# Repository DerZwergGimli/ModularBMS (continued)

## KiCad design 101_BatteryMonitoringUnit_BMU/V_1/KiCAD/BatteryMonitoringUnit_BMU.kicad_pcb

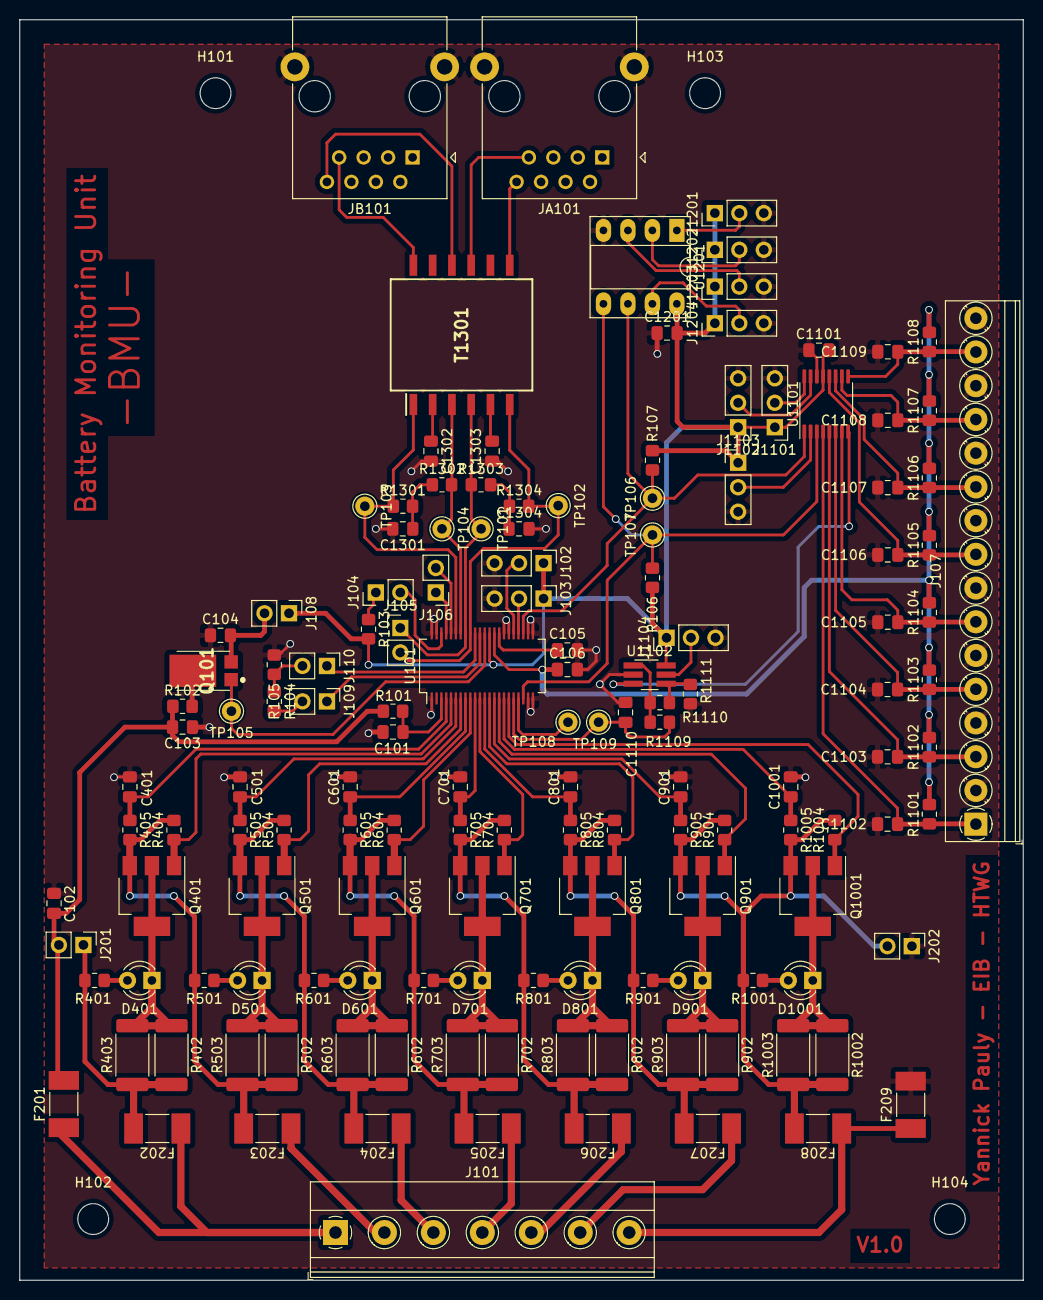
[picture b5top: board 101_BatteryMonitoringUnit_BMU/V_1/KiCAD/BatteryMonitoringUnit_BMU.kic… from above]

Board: 2 copper layers, 104.1 x 130.8 mm, 149 parts (0 on the bottom side), 96 nets.

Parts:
C101, C1101, C1201: 100nF; C_0805_2012Metric_Pad1.18x1.45mm_HandSolder
C102, C1102, C1103, C1104, C1105, C1106, C1107, C1108, C1109: 10nF*; C_0805_2012Metric_Pad1.18x1.45mm_HandSolder
C103: 0.1u; C_0805_2012Metric_Pad1.18x1.45mm_HandSolder
C104, C105, C106: 1uF; C_0805_2012Metric_Pad1.18x1.45mm_HandSolder
C401, C501, C601, C701, C801, C901, C1001: 10nF/30V; C_0805_2012Metric_Pad1.18x1.45mm_HandSolder
C1110, C1301, C1302, C1303, C1304: 10nF; C_0805_2012Metric_Pad1.18x1.45mm_HandSolder
D401, D501, D601, D701, D801, D901, D1001: LED_Dis; LED_D3.0mm
F201, F209: Fuse_0.5A; Fuse_Littelfuse-NANO2-451_453
F202, F203, F204, F205, F206, F207, F208: Fuse_0.25A; Fuse_Littelfuse-NANO2-451_453
H101, H102, H103, H104: MountingHole; MountingHole_3.2mm_M3_DIN965
J101: BalancingConnect; TerminalBlock_Phoenix_MKDS-1,5-7-5.08_1x07_P5.08mm_Horizont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
J102: isoSPI/SPI; PinHeader_1x03_P2.54mm_Vertical
J103: DischargeTimer; PinHeader_1x03_P2.54mm_Vertical
J104: WatchdogTimer; PinHeader_1x02_P2.54mm_Vertical
J105: SerialInterface_1; PinHeader_1x02_P2.54mm_Vertical
J106: SerialInterface_0; PinHeader_1x02_P2.54mm_Vertical
J107: NTC_10k; TerminalBlock_Phoenix_PT-1,5-16-3.5-H_1x16_P3.50mm_Horizont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
J108: V_REG; PinHeader_1x02_P2.54mm_Vertical
J109: I_BIAS; PinHeader_1x02_P2.54mm_Vertical
J110: I_CMP; PinHeader_1x02_P2.54mm_Vertical
J201: FusedBATT+; PinHeader_1x02_P2.54mm_Vertical
J202: FusedBATT-; PinHeader_1x02_P2.54mm_Vertical
J1101: Temp_A0; PinHeader_1x03_P2.54mm_Vertical
J1102: Temp_A1; PinHeader_1x03_P2.54mm_Vertical
J1103: Temp_~RESET; PinHeader_1x03_P2.54mm_Vertical
J1104: Temp_~SHDN; PinHeader_1x03_P2.54mm_Vertical
J1201: EEPROM_A0; PinHeader_1x03_P2.54mm_Vertical
J1202: EEPROM_A1; PinHeader_1x03_P2.54mm_Vertical
J1203: EEPROM_A2; PinHeader_1x03_P2.54mm_Vertical
J1204: EEPROM_~ENABLE; PinHeader_1x03_P2.54mm_Vertical
JA101: isoSPI_IN; RJ45_C
JB101: isoSPI_OUT; RJ45_C
Q101: DXT5551P5-13; DXT5551P513
Q401, Q501, Q601, Q701, Q801, Q901, Q1001: PZT2222A; SOT-223-3_TabPin2
R101: 10; R_0805_2012Metric_Pad1.20x1.40mm_HandSolder
R102, R405, R505, R605, R705, R805, R905, R1005, R1109: 100; R_0805_2012Metric_Pad1.20x1.40mm_HandSolder
R103: 1M; R_0805_2012Metric_Pad1.20x1.40mm_HandSolder
R104, R105, R404, R504, R604, R704, R804, R904, R1004: 1k; R_0805_2012Metric_Pad1.20x1.40mm_HandSolder
R106, R107, R1101, R1102, R1103, R1104, R1105, R1106, R1107, R1108, R1111: 10k; R_0805_2012Metric_Pad1.20x1.40mm_HandSolder
R401, R501, R601, R701, R801, R901, R1001: Rv_LED; R_0805_2012Metric_Pad1.20x1.40mm_HandSolder
R402, R403, R502, R503, R602, R603, R702, R703, R802, R803, R902, R903, R1002, R1003: R_Dis; R_2512_6332Metric_Pad1.40x3.35mm_HandSolder
R1110: 0; R_0805_2012Metric_Pad1.20x1.40mm_HandSolder
R1301, R1302, R1303, R1304: 49.9; R_0805_2012Metric_Pad1.20x1.40mm_HandSolder
T1301: HM2112ZNL; SOP200P1543X320-12N
TP101, TP102, TP103, TP104, TP105, TP106, TP107, TP108, TP109: TestPoint; Pin_D1.0mm_L10.0mm
U101: LTC6810-1_mod; SSOP-44_5.3x12.8mm_P0.5mm
U1101: ADG728; TSSOP-16_4.4x5mm_P0.65mm
U1102: LTC6255; TSOT-23-6_HandSoldering
U1201: 24LC256; DIP-8_W7.62mm_Socket_LongPads

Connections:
+BATT: F201.1, F202.1, J101.1
-BATT: F208.1, F209.1, J101.7
/BalanceFuses/FusedCell_0: F208.2, J202.2, Q901.3, Q1001.3, R904.2, R905.2, R1001.1, R1002.2, R1003.1, R1004.2, R1005.2
/BalanceFuses/FusedCell_1: F207.2, Q801.3, R804.2, R805.2, R901.1, R902.2, R903.1
/BalanceFuses/FusedCell_2: F206.2, Q701.3, R704.2, R705.2, R801.1, R802.2, R803.1
/BalanceFuses/FusedCell_3: F205.2, Q601.3, R604.2, R605.2, R701.1, R702.2, R703.1
/BalanceFuses/FusedCell_4: F204.2, Q501.3, R504.2, R505.2, R601.1, R602.2, R603.1
/BalanceFuses/FusedCell_5: F203.2, Q401.3, R404.2, R405.2, R501.1, R502.2, R503.1
/BalanceFuses/FusedCell_6: F202.2, J201.1, R401.1, R402.2, R403.1
/C_0: C1001.1, R1005.1, U101.16
/C_1: C901.1, R905.1, U101.14
/C_2: C801.1, R805.1, U101.12
/C_3: C701.1, R705.1, U101.10
/C_4: C601.1, R605.1, U101.8
/C_5: C501.1, R505.1, U101.6
/C_6: C401.1, R405.1, U101.4
/Cell_1: F207.1, J101.6
/Cell_2: F206.1, J101.5
/Cell_3: F205.1, J101.4
/Cell_4: F204.1, J101.3
/Cell_5: F203.1, J101.2
/EEPROM_I2C/A0: J1201.2, U1201.1
/EEPROM_I2C/A1: J1202.2, U1201.2
/EEPROM_I2C/A2: J1203.2, U1201.3
/EEPROM_I2C/~ENABLE: J1204.2, U1201.7
/MUX_I2C/A0: J1101.2, U1101.16
/MUX_I2C/A1: J1102.2, U1101.15
/MUX_I2C/~RESET: J1103.2, U1101.2
/MUX_I2C/~SHDN: J1104.2, U1102.5
/NTC_0: C1102.1, J107.1, R1101.1, U1101.4
/NTC_1: C1103.1, J107.3, R1102.1, U1101.5
/NTC_2: C1104.1, J107.5, R1103.1, U1101.6
/NTC_3: C1105.1, J107.7, R1104.1, U1101.7
/NTC_4: C1106.1, J107.9, R1105.1, U1101.12
/NTC_5: C1107.1, J107.11, R1106.1, U1101.11
/NTC_6: C1108.1, J107.13, R1107.1, U1101.10
/NTC_7: C1109.1, J107.15, R1108.1, U1101.9
/S_0: Q1001.1, R1004.1, U101.17
/S_1: Q901.1, R904.1, U101.15
/S_2: Q801.1, R804.1, U101.13
/S_3: Q701.1, R704.1, U101.11
/S_4: Q601.1, R604.1, U101.9
/S_5: Q501.1, R504.1, U101.7
/S_6: Q401.1, R404.1, U101.5
/isoSPI/isoSPI_IN+_Header: JA101.7, T1301.9
/isoSPI/isoSPI_IN-_Header: JA101.8, T1301.7
/isoSPI/isoSPI_OUT+_Header: JB101.7, T1301.12
/isoSPI/isoSPI_OUT-_Header: JB101.8, T1301.10
DRIVE: Q101.1, TP105.1, U101.33
DTEN: J103.2, U101.26
GND: C101.1, C102.2, C103.1, C104.1, C105.2, C106.2, C401.2, C501.2, C601.2, C701.2, C801.2, C901.2, C1001.2, C1101.1, C1102.2, C1103.2, C1104.2, C1105.2, C1106.2, C1107.2, C1108.2, C1109.2, C1110.2, C1201.1, C1301.2, C1302.2, C1303.1, C1304.2, F209.2, J102.3, J103.3, J107.2, J107.4, J107.6, J107.8, J107.10, J107.12, J107.14, J107.16, J202.1, J1101.3, J1102.3, J1103.3, J1104.3, J1201.3, J1202.3, J1203.3, J1204.3, JA101.SH, JB101.SH, R105.1, R1111.2, U101.1, U101.21, U101.22, U101.23, U101.24, U101.28, U101.29, U101.43, U101.44, U1101.14, U1102.2, U1201.4
GPIO1_(ADC): C1110.1, R1109.2, TP109.1, U101.18
GPIO2_(ADC): TP108.1, U101.19
GPIO3_(SDA): R106.1, TP107.1, U101.20, U1101.3, U1201.5
GPIO4_(SCL): R107.1, TP106.1, U101.25, U1101.1, U1201.6
IBIAS: J109.1, U101.34
ICMP: J110.1, U101.35
ISOMD: J102.2, U101.27
unnamed: C101.2, R101.1, U101.3
unnamed: C104.2, J108.2, Q101.2
unnamed: C1301.1, R1301.2, R1302.1
unnamed: C1302.1, T1301.2
unnamed: C1303.2, T1301.5
unnamed: C1304.1, R1303.2, R1304.1
unnamed: D401.1, Q401.2, R402.1, R403.2
unnamed: D401.2, R401.2
unnamed: D501.1, Q501.2, R502.1, R503.2
unnamed: D501.2, R501.2
unnamed: D601.1, Q601.2, R602.1, R603.2
unnamed: D601.2, R601.2
unnamed: D701.1, Q701.2, R702.1, R703.2
unnamed: D701.2, R701.2
unnamed: D801.1, Q801.2, R802.1, R803.2
unnamed: D801.2, R801.2
unnamed: D901.1, Q901.2, R902.1, R903.2
unnamed: D901.2, R901.2
unnamed: D1001.1, Q1001.2, R1002.1, R1003.2
unnamed: D1001.2, R1001.2
unnamed: J104.1, R103.1
unnamed: J109.2, R104.2
unnamed: J110.2, R104.1, R105.2
unnamed: Q101.3, R102.2
unnamed: R1109.1, R1110.1, U1102.1
unnamed: R1110.2, R1111.1, U1102.4
unnamed: U1101.8, U1102.3
Serial_CLK: J106.1, U101.41
Serial_MISO: J105.1, R1303.1, T1301.4, TP101.1, U101.37
Serial_MOSI: J106.2, U101.40
Serial_~CS: J105.2, R1304.2, T1301.6, TP102.1, U101.36
VCC: C102.1, C103.2, F201.2, J201.2, R101.2, R102.1
V_Ref1: C105.1, U101.30
V_Ref2: C106.1, R1101.2, R1102.2, R1103.2, R1104.2, R1105.2, R1106.2, R1107.2, R1108.2, U101.31
V_Reg: C1101.2, C1201.2, J102.1, J103.1, J108.1, J1101.1, J1102.1, J1103.1, J1104.1, J1201.1, J1202.1, J1203.1, J1204.1, R103.2, R106.2, R107.2, U101.32, U1101.13, U1102.6, U1201.8
WDT: J104.2, U101.42
isoSPI+_OUT: R1301.1, T1301.1, TP103.1, U101.39
isoSPI-_OUT: R1302.2, T1301.3, TP104.1, U101.38

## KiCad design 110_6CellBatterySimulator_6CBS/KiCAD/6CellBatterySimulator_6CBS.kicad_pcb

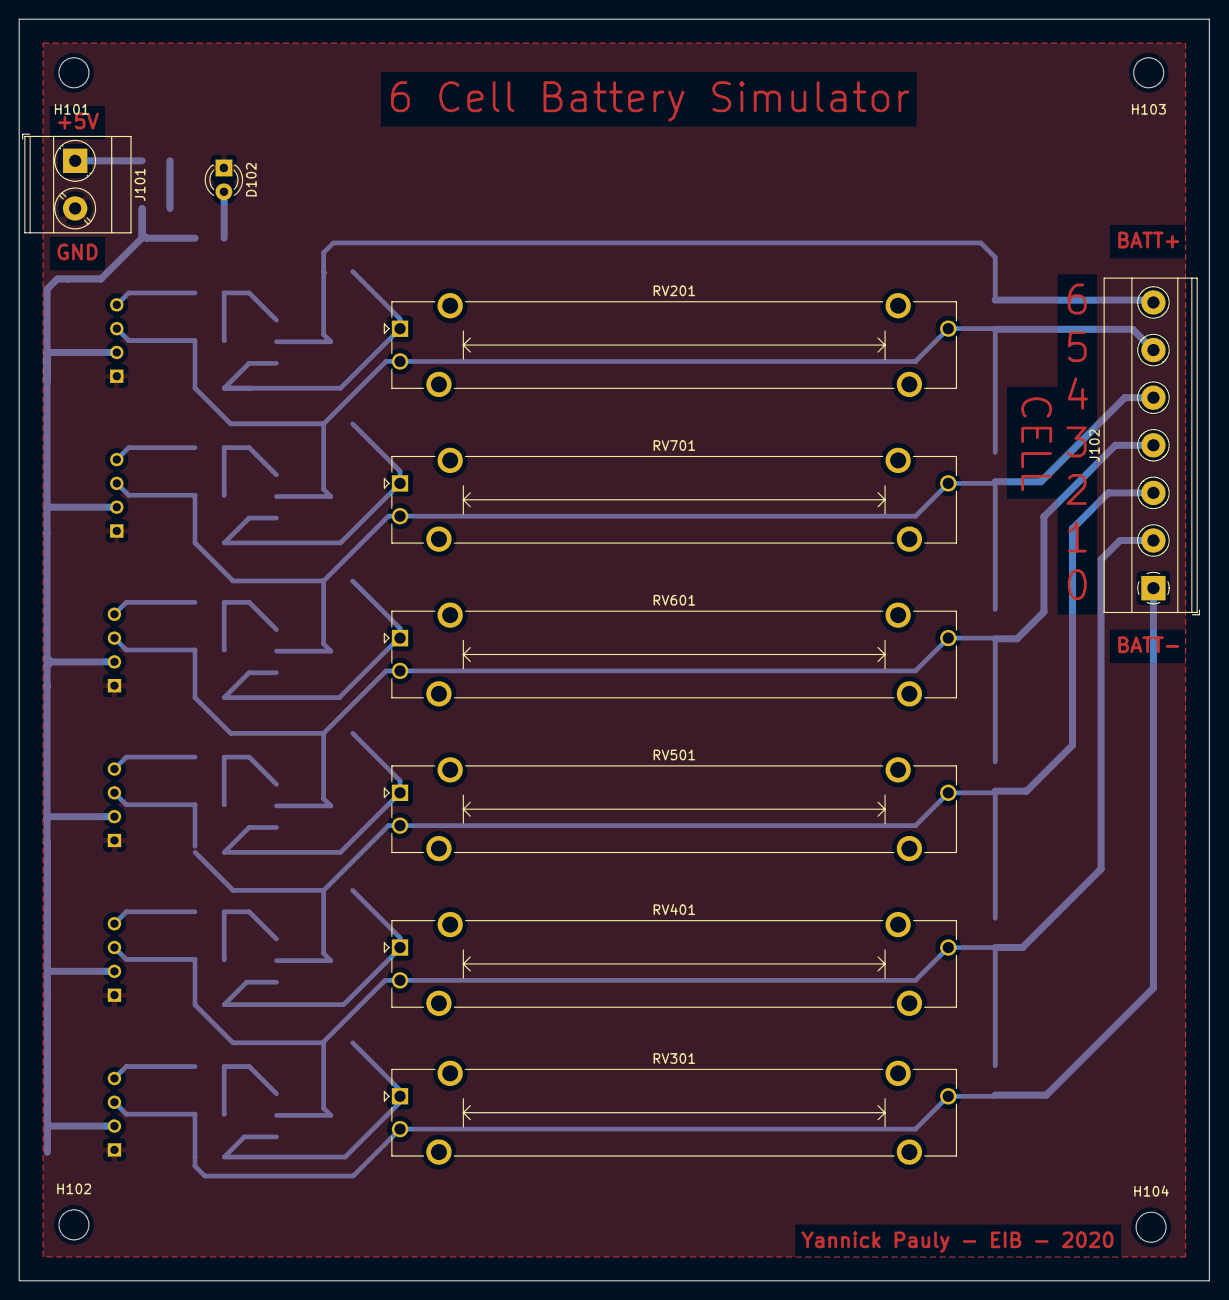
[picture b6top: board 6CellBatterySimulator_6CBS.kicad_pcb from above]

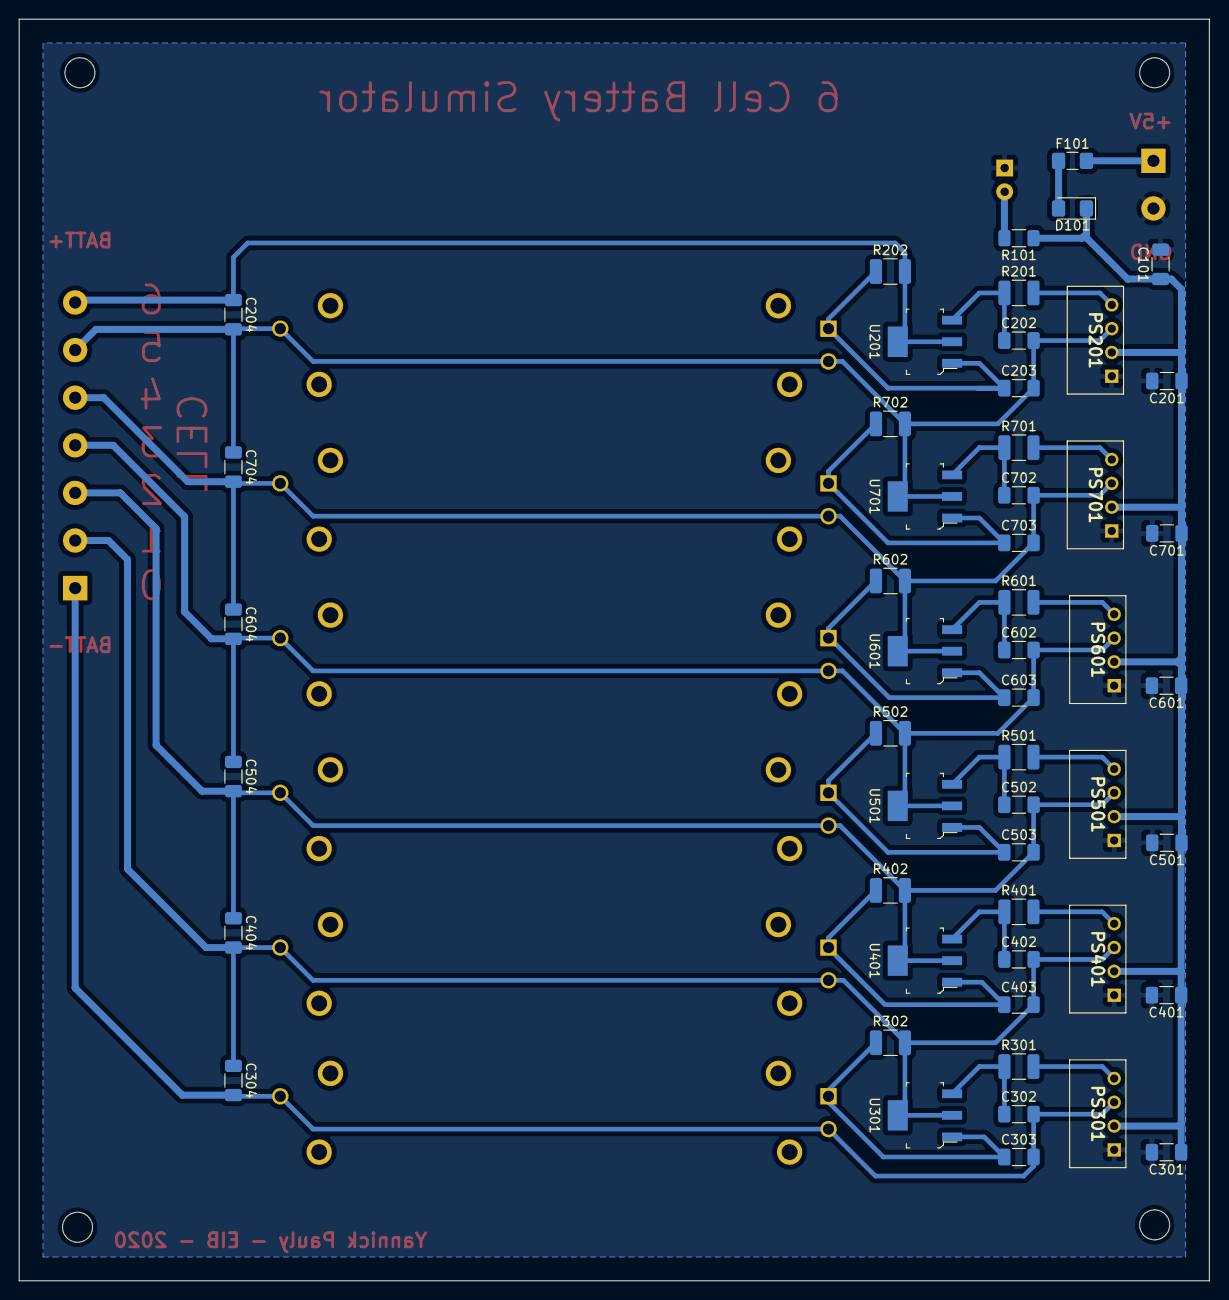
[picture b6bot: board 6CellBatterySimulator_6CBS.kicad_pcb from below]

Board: 2 copper layers, 127.0 x 134.6 mm, 65 parts (52 on the bottom side), 30 nets.

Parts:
C101: 47u; C_1206_3216Metric_Pad1.33x1.80mm_HandSolder
C201, C301, C401, C501, C601, C701: 10u*; C_1206_3216Metric_Pad1.33x1.80mm_HandSolder
C202, C302, C402, C502, C602, C702: 0.1u*; C_1206_3216Metric_Pad1.33x1.80mm_HandSolder
C203, C303, C403, C503, C603, C703: 1u*; C_1206_3216Metric_Pad1.33x1.80mm_HandSolder
C204, C304, C404, C504, C604, C704: 100u; C_1206_3216Metric_Pad1.33x1.80mm_HandSolder
D101: 40V 2A; D_1206_3216Metric_Pad1.42x1.75mm_HandSolder
D102: LED; LED_D3.0mm
F101: 4A; Fuse_1206_3216Metric_Pad1.42x1.75mm_HandSolder
H101, H102, H103, H104: MountingHole; MountingHole_3.2mm_M3_DIN965
J101: Screw_Terminal_01x02; TerminalBlock_Phoenix_MKDS-3-2-5.08_1x02_P5.08mm_Horizontal
J102: Screw_Terminal_01x07; TerminalBlock_Phoenix_MKDS-1,5-7-5.08_1x07_P5.08mm_Horizont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
PS201, PS301, PS401, PS501, PS601, PS701: ROE-0512S; ROE1205S
R101: 330; R_1206_3216Metric_Pad1.30x1.75mm_HandSolder
R201, R301, R401, R501, R601, R701: 22; R_1210_3225Metric_Pad1.30x2.65mm_HandSolder
R202, R302, R402, R502, R602, R702: 340; R_1210_3225Metric_Pad1.30x2.65mm_HandSolder
RV201, RV301, RV401, RV501, RV601, RV701: 1k; Potentiometer_Bourns_PTA4543_Single_Slide
U201, U301, U401, U501, U601, U701: LM317DCYR; SOT-223-4

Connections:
+5V: C101.1, C201.1, C301.1, C401.1, C501.1, C601.1, C701.1, D101.1, PS201.2, PS301.2, PS401.2, PS501.2, PS601.2, PS701.2, R101.1
/Channel1/OUT+: C304.1, C402.2, C403.2, C404.2, J102.2, PS401.3, R302.2, RV401.2, RV401.3, U301.2, U301.4
/Channel1/OUT-: C302.2, C303.2, C304.2, J102.1, PS301.3, RV301.2, RV301.3
/Channel2/OUT+: C404.1, C502.2, C503.2, C504.2, J102.3, PS501.3, R402.2, RV501.2, RV501.3, U401.2, U401.4
/Channel3/OUT+: C504.1, C602.2, C603.2, C604.2, J102.4, PS601.3, R502.2, RV601.2, RV601.3, U501.2, U501.4
/Channel4/OUT+: C604.1, C702.2, C703.2, C704.2, J102.5, PS701.3, R602.2, RV701.2, RV701.3, U601.2, U601.4
/Channel5/OUT+: C202.2, C203.2, C204.2, C704.1, J102.6, PS201.3, R702.2, RV201.2, RV201.3, U701.2, U701.4
/Channel6/OUT+: C204.1, J102.7, R202.2, U201.2, U201.4
GND: C101.2, C201.2, C301.2, C401.2, C501.2, C601.2, C701.2, D102.1, J101.2, PS201.1, PS301.1, PS401.1, PS501.1, PS601.1, PS701.1
unnamed: C202.1, R201.1, U201.3
unnamed: C203.1, R202.1, RV201.1, U201.1
unnamed: C302.1, R301.1, U301.3
unnamed: C303.1, R302.1, RV301.1, U301.1
unnamed: C402.1, R401.1, U401.3
unnamed: C403.1, R402.1, RV401.1, U401.1
unnamed: C502.1, R501.1, U501.3
unnamed: C503.1, R502.1, RV501.1, U501.1
unnamed: C602.1, R601.1, U601.3
unnamed: C603.1, R602.1, RV601.1, U601.1
unnamed: C702.1, R701.1, U701.3
unnamed: C703.1, R702.1, RV701.1, U701.1
unnamed: D101.2, F101.1
unnamed: D102.2, R101.2
unnamed: F101.2, J101.1
unnamed: PS201.4, R201.2
unnamed: PS301.4, R301.2
unnamed: PS401.4, R401.2
unnamed: PS501.4, R501.2
unnamed: PS601.4, R601.2
unnamed: PS701.4, R701.2

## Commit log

2020-10-29 added files
2020-10-29 changed file name
2020-10-29 added bms
2020-10-29 added new files
2020-11-02 added new modules
2020-11-05 erste platienen bestellt
2020-11-05 added Lib
2020-11-08 ltspice again
2020-11-08 added new BJB
2020-11-09 Mon. Done a Lot of recouvery
2020-11-10 some small chages in 7CBS
2020-11-10 added code
2020-11-10 added submodel
2020-11-10 added all
